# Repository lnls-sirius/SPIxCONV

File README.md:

# SPIxCONV

This project consists of an 18-bit analog input (ADC) and output (DAC) within a range of 20 V (± 10 V) and 32 digital pins that can be either as inputs or outputs. This system interfaces with pulsed power electronics hardware in order to control the output voltage for pulsed magnets as well as read and write status commands to their power supplies. An operator interface (OPI) software based on Qt was also developed for remote control.

<!--========================================-->
## Hardware
<!--========================================-->

<!--==============================-->
### Main Board
<!--==============================-->

<!--====================-->
#### Circuit
<!--====================-->

  - Board

  - CPLD

  - DAC

  - ADC

  - Digital I/O

<!--====================-->
#### PCB
<!--====================-->

<!--====================-->
#### Connectors
<!--====================-->

  - SPIxxCON

  - CPLD

  - Board Connection Link

<!--====================-->
#### Test Points
<!--====================-->

  - SPI

  - Power Voltage

  - Analog In/Out

<!--====================-->
#### BOM
<!--====================-->
Bill of materials

<!--==============================-->
### GPIO Expander Board
<!--==============================-->

<!--====================-->
#### Circuit
<!--====================-->

<!--====================-->
#### PCB
<!--====================-->

<!--====================-->
#### Connectors
<!--====================-->

  - Interface A/B

  - Interface C/D

<!--====================-->
#### Test Points
<!--====================-->

  - Power Voltage

  - Analog In/Out

<!--====================-->
#### BOM
<!--====================-->
Bill of materials

<!--====================-->
### Identification
<!--====================-->

<!--========================================-->
### Software
<!--========================================-->

The software files of this project related to the server-side (IOC) is now available at [streamdevice-ioc](https://github.com/lnls-sirius/streamdevice-ioc) GitHub's repository under the "spixconv" directory.

The software files related to the OPI (Operator Interface) is now at [pydm-opi](https://github.com/lnls-sirius/pydm-opi) GitHub's repository.

Finally, the client-side (Python code) is at this repository under the [scripts](https://github.com/lnls-sirius/SPIxCONV/tree/master/software/scripts) directory.

<!--====================-->
#### Brief Description
<!--====================-->
To remotely control the board an [EPICS](https://epics-controls.org/about-epics/) IOC with an OPI was developed.

The IOC was built using [asynDriver](https://epics.anl.gov/modules/soft/asyn/) and [StreamDevice](http://epics.web.psi.ch/software/streamdevice/) on top of it. The application is launched in a form of a Docker container. The Docker image can be found at [Docker Hub](https://hub.docker.com/repository/docker/lnlscon/streamdevice-ioc) with the tag "SPIxCONV" followed by the version (eg: SPIxCONV-v1.9.6).

To configure the parameters of the IOC a [spreadsheet](https://cnpemcamp.sharepoint.com/:x:/s/controle/EUG0_4JUaz9Au7kZNcMZwZQB1x5OJBN_1QMdbbCGJ1Driw?e=Po8LNr) is used (available for CNPEM accounts only). PV's prefix, Power Supply voltage, host IP to connect to, scan rate and other settings can be adjusted. 

<!--====================-->
#### OPI (Operator Interface)
<!--====================-->

Previously, [Control System Studio](http://controlsystemstudio.org/) was used to develop the OPI. The windows can still be found under the [CSS](https://github.com/lnls-sirius/SPIxCONV/tree/master/software/CSS) directory. Lately, we have been using [PyDM (Python Display Manager)](https://slaclab.github.io/pydm/) to develop the windows. As stated before, the files related to the PyDM OPI is located in [pydm-opi](https://github.com/lnls-sirius/pydm-opi) repository.

<!--====================-->
#### CPLD
<!--====================-->

<!--====================-->
#### Board Calibration
<!--====================-->

To achieve more confiability, a calibration is done considering the DAC adjusts and the ADC measures. The next figures show the setup for this procedure. We basically connect the DAC output to the voltmeter and to the ADC input simultaneously.

  - DAC calibration:
To calibrate the DAC we set its output to -9 V and later to +9 V and measure the real output voltage with the help of a 7 ½ digit voltmeter (here we are using the [Keysight 34420A](https://github.com/lnls-sirius/SPIxCONV/blob/master/documentation/Keysight%2034420A%20datasheet.pdf). We then use both measures to calculate the angular and linear coeffients for this curve.

  - ADC calibration:
Now that we have the DAC calibrated, we will use its output to calibrate the ADC coefficients. Again, we set the DAC output to -9 V (already considering the corrections), wait 60 s for thermal stabilization and read the voltage with the ADC. We then repeat the procedure for an adjustment of +9 V on the DAC output. Finally, these measures are used to calculate an angular and linear coefficient for the ADC.

An automated script was developed for this process. To control the voltmeter 34420A remotely we need a RS-232/USB adaptor to plug it in the USB connector of the BeagleBone Black. An important thing to note, is that the serial cable (RS-232) has an identification to show which side is the voltmeter's one and which should be connected to the adaptor.

Finally, to calibrate the board, just connect to the BeagleBone Black and run the appropriate scrips, as showed below:

```console
$ ssh root@<BBB-IP>
root@beaglebone:~# systemctl stop bbb-function
root@beaglebone:~# /root/spixconv/software/scripts/calibration.py <BOARD-ID>
    gain = 1.00014284735
    offset = -15.81235112
    gain = 1.00052568324
    offset = -66.6829873034
```

Where <BBB-IP> is the BeagleBone IP (for example "192.168.7.2") and the <BOARD-ID> is the identification of the board (for example "15").

| Board ID |   DAC gain    |  DAC offset   |   ADC gain    |   ADC offset   |    Date    |
| :------: | :-----------: | :-----------: | :-----------: | :------------: | :--------: |
|     1    | 1.00022856796 | -23.604551795 | 1.00031151483 | -25.5034979525 | 06/14/2018 |
|     2    | 1.00026576963 | -28.880179670 | 1.00047415222 | -60.2158137830 | 06/14/2018 |
|     3    | 1.00030796599 | -32.699603180 | 1.00041814300 | -47.9227113769 | 06/18/2018 |
|     4    | 1.00017479634 | -17.242341185 | 1.00026390485 | -31.6174014794 | 06/19/2018 |
|     5    | 1.00017265115 | -13.974728690 | 1.00045784906 | -39.5533800101 | 06/19/2018 |
|     6    | 1.00015184443 | -11.674423865 | 1.00060158655 | -59.1729212883 | 06/19/2018 |
|     7    | 1.00019784934 | -20.918896760 | 1.00029330340 | -24.4439584471 | 06/19/2018 |
|     8    | 1.00035674834 | -37.769448800 | 1.00029168671 | -34.0324363824 | 06/19/2018 |
|     9    | 1.00023135812 | -26.566767695 | 1.00045023944 | -44.5911926966 | 06/19/2018 |
|    10    | 1.00020592482 | -21.571632830 | 1.00044201352 | -51.3525871959 | 06/19/2018 |
|    11    | 1.00014897135 | -16.862233835 | 1.00067934214 | -81.2456900362 | 06/19/2018 |
|    12    | 1.00022598345 | -22.008100925 | 1.00057691743 | -66.0110325831 | 06/19/2018 |
|    13    | 1.00032333122 | -33.267142775 | 1.00039023957 | -45.3552208747 | 06/19/2018 |
|    14    | 1.00016016368 | -18.311884625 | 1.00048566801 | -60.5575726483 | 06/19/2018 |
|    15    | 1.00022607238 | -22.051354520 | 1.00046470661 | -58.5770907625 | 06/19/2018 |
|    16    | 1.00028974958 | -32.626203140 | 1.00073037347 | -97.7370251289 | 06/19/2018 |
|    17    | 1.00027075563 | -27.292903805 | 1.00037276504 | -34.2682222150 | 06/20/2018 |
|    18    | 1.00017256223 | -15.753368945 | 1.00046720927 | -66.4461854942 | 06/20/2018 |
|    19    | 1.00023103020 | -24.296609315 | 1.00032961706 | -28.7417520711 | 06/20/2018 |
|    20    | 1.00019010191 | -20.998850375 | 1.00012983616 | -2.10309904365 | 06/20/2018 |

<!--====================-->
#### Code
<!--====================-->
[https://lnls-sirius.github.io/SPIxCONV/](https://lnls-sirius.github.io/SPIxCONV/)

<!--========================================-->
### Known Problems
<!--========================================-->

  - Not connecting to IOC after BBB reboots:  
    Status: both nodes (IOC and BBB) show they are connected, but the IOC does not respond.
    Solution: reboot IOC.

  - Flash memory loses data:
    Status: this happened once in three years. After a power cycle, the flash suddenly lost al its data!
    Solution: record information in flash memory again.

<!--========================================-->
### FAQ
<!--========================================-->

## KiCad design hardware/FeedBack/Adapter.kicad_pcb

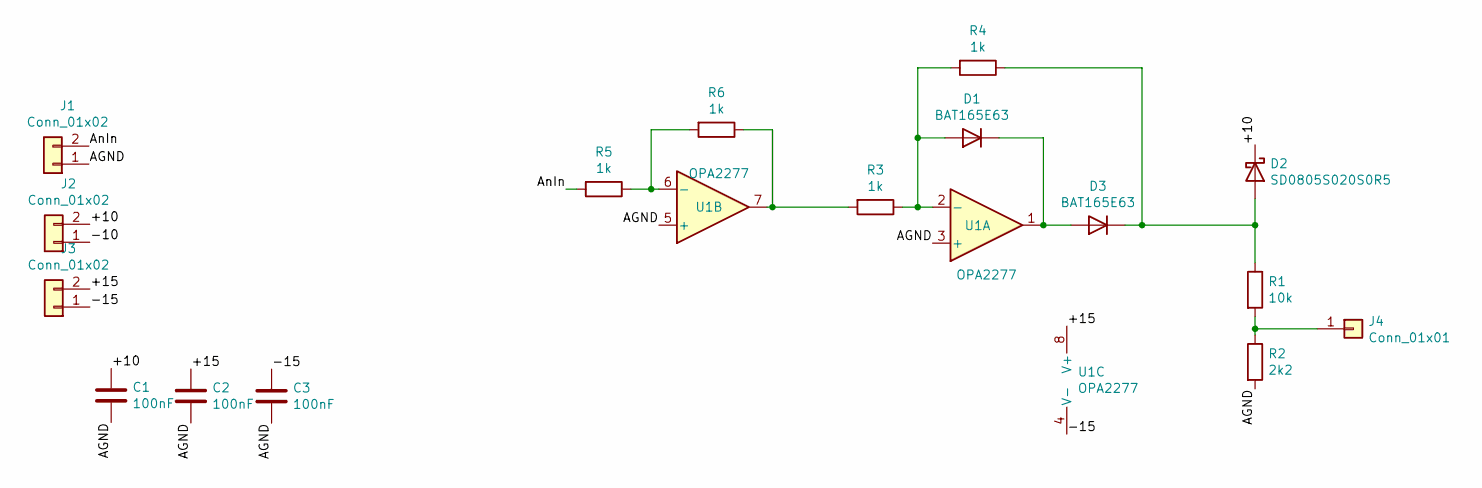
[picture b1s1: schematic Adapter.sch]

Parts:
C1, C2, C3: 100nF; C_0805_2012Metric_Pad1.18x1.45mm_HandSolder
D1, D3: BAT165E63; D_0805_2012Metric_Pad1.15x1.40mm_HandSolder
D2: SD0805S020S0R5; D_0805_2012Metric_Pad1.15x1.40mm_HandSolder
J1, J2, J3: Conn_01x02; PinSocket_1x02_P2.54mm_Vertical
J4: Conn_01x01; PinSocket_1x01_P2.54mm_Vertical
R1: 10k; R_0805_2012Metric_Pad1.20x1.40mm_HandSolder
R2: 2k2; R_0805_2012Metric_Pad1.20x1.40mm_HandSolder
R3, R4, R5, R6: 1k; R_0805_2012Metric_Pad1.20x1.40mm_HandSolder
U1: OPA2277; SOIC-8_3.9x4.9mm_P1.27mm

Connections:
/+10: C1.1, D2.1 (K), J2.2
/+15: C2.1, J3.2, U1.8 (V+)
/-10: J2.1
/-15: C3.1, J3.1, U1.4 (V-)
/AGND: C1.2, C2.2, C3.2, J1.1, R2.2, U1.3 (+), U1.5 (+)
/AnIn: J1.2, R5.2
unnamed: D1.1 (K), D3.2 (A), U1.1
unnamed: D1.2 (A), R3.1, R4.2, U1.2 (-)
unnamed: D2.2 (A), D3.1 (K), R1.1, R4.1
unnamed: J4.1, R1.2, R2.1
unnamed: R3.2, R6.1, U1.7
unnamed: R5.1, R6.2, U1.6 (-)

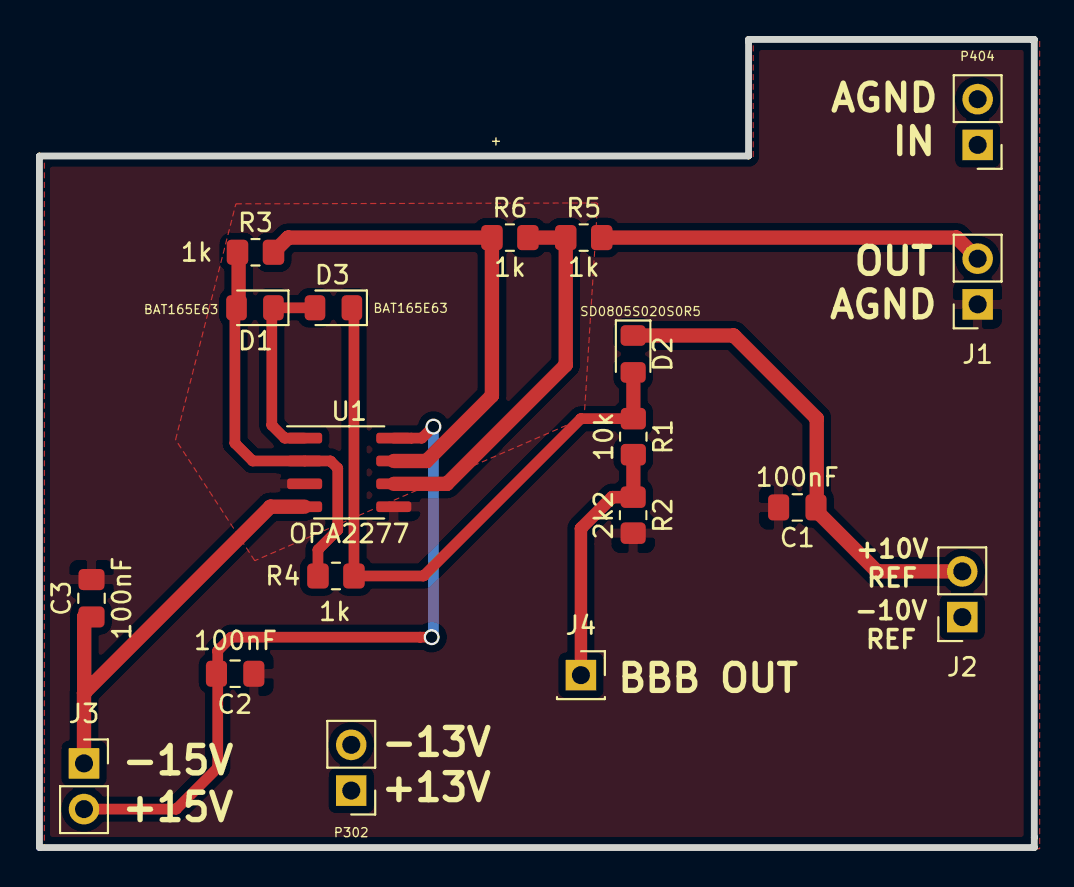
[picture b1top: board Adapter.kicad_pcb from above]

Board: 2 copper layers, 55.3 x 44.9 mm, 19 parts (0 on the bottom side), 11 nets.

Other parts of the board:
P302: CONN_01X02; Pin_Header_Straight_1x02_Pitch2.54mm
P404: Analog_in; Pin_Header_Straight_1x02_Pitch2.54mm

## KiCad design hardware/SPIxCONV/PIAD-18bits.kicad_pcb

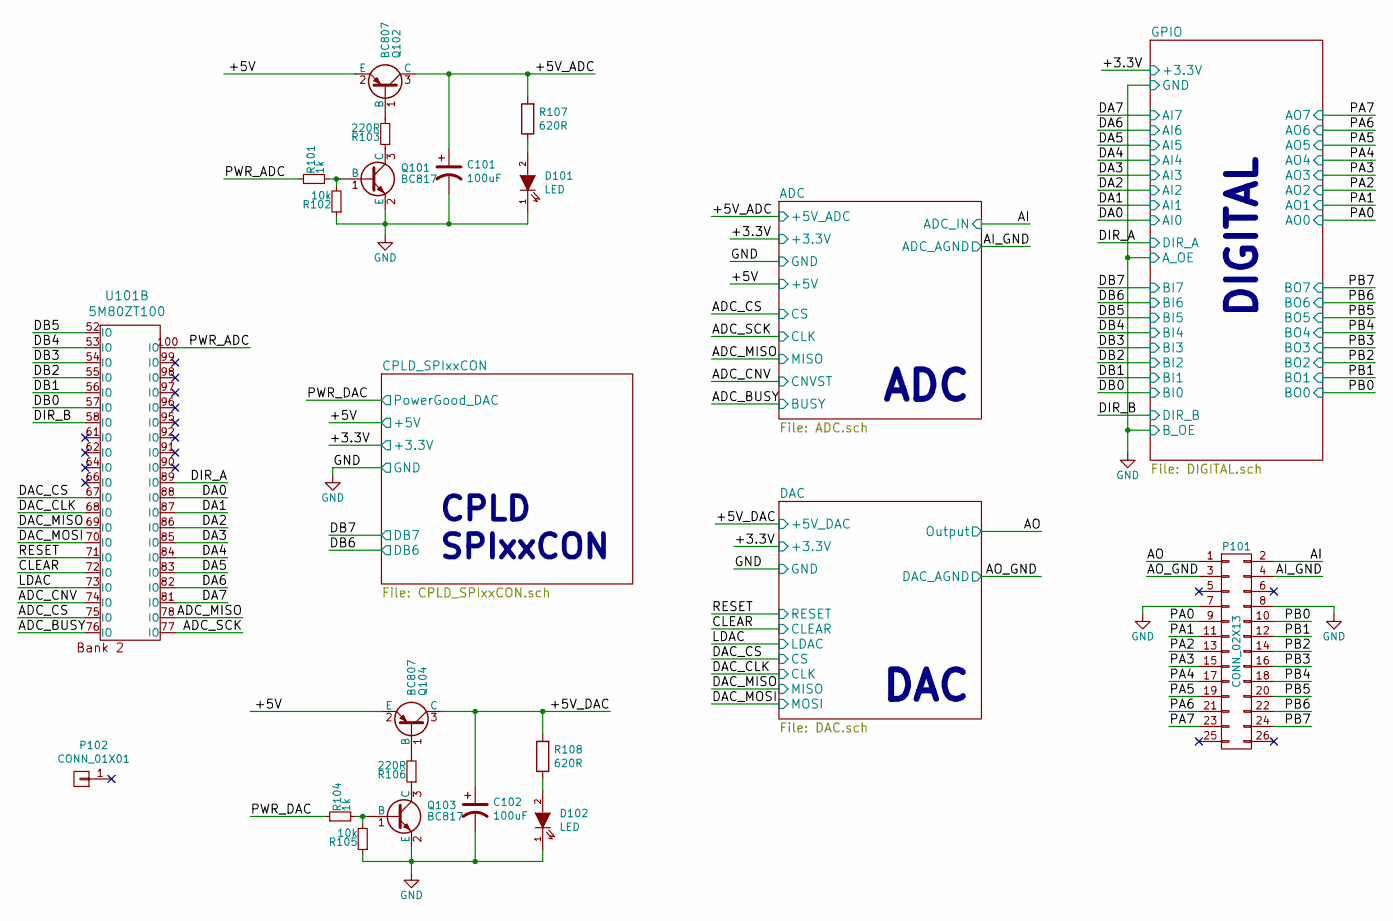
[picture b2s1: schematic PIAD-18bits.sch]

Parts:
C101, C102: 100uF; CP_Elec_6.3x5.3
D101, D102: LED; LED_0805
P101: CONN_02X13; Pin_Header_Straight_2x13_Pitch2.54mm
P102: CONN_01X01; LNLS_LOGO_Silk
Q101, Q103: BC817; SOT-23
Q102, Q104: BC807; SOT-23
R101, R104: 1k; R_0805
R102, R105: 10k; R_0805
R103, R106: 220R; R_0805
R107, R108: 620R; R_0805
U101: 5M80ZT100; TQFP-100_14x14mm_Pitch0.5mm

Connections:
+5V: Q102.2 (E), Q104.2 (E); also elsewhere on the board
/+5V_ADC: C101.1, Q102.3 (C), R107.2; also elsewhere on the board
/+5V_DAC: C102.1, Q104.3 (C), R108.2; also elsewhere on the board
/ADC_BUSY: U101.76 (IO); also elsewhere on the board
/ADC_CNV: U101.74 (IO); also elsewhere on the board
/ADC_CS: U101.75 (IO); also elsewhere on the board
/ADC_MISO: U101.78 (IO); also elsewhere on the board
/ADC_SCK: U101.77 (IO); also elsewhere on the board
/AI: P101.2; also elsewhere on the board
/AI_GND: P101.4; also elsewhere on the board
/AO: P101.1; also elsewhere on the board
/AO_GND: P101.3; also elsewhere on the board
/CLEAR: U101.72 (IO); also elsewhere on the board
/DA0: U101.88 (IO); also elsewhere on the board
/DA1: U101.87 (IO); also elsewhere on the board
/DA2: U101.86 (IO); also elsewhere on the board
/DA3: U101.85 (IO); also elsewhere on the board
/DA4: U101.84 (IO); also elsewhere on the board
/DA5: U101.83 (IO); also elsewhere on the board
/DA6: U101.82 (IO); also elsewhere on the board
/DA7: U101.81 (IO); also elsewhere on the board
/DAC_CLK: U101.68 (IO); also elsewhere on the board
/DAC_CS: U101.67 (IO); also elsewhere on the board
/DAC_MISO: U101.69 (IO); also elsewhere on the board
/DAC_MOSI: U101.70 (IO); also elsewhere on the board
/DB0: U101.57 (IO); also elsewhere on the board
/DB1: U101.56 (IO); also elsewhere on the board
/DB2: U101.55 (IO); also elsewhere on the board
/DB3: U101.54 (IO); also elsewhere on the board
/DB4: U101.53 (IO); also elsewhere on the board
/DB5: U101.52 (IO); also elsewhere on the board
/DIR_A: U101.89 (IO); also elsewhere on the board
/DIR_B: U101.58 (IO); also elsewhere on the board
/LDAC: U101.73 (IO); also elsewhere on the board
/PA0: P101.9; also elsewhere on the board
/PA1: P101.11; also elsewhere on the board
/PA2: P101.13; also elsewhere on the board
/PA3: P101.15; also elsewhere on the board
/PA4: P101.17; also elsewhere on the board
/PA5: P101.19; also elsewhere on the board
/PA6: P101.21; also elsewhere on the board
/PA7: P101.23; also elsewhere on the board
/PB0: P101.10; also elsewhere on the board
/PB1: P101.12; also elsewhere on the board
/PB2: P101.14; also elsewhere on the board
/PB3: P101.16; also elsewhere on the board
/PB4: P101.18; also elsewhere on the board
/PB5: P101.20; also elsewhere on the board
/PB6: P101.22; also elsewhere on the board
/PB7: P101.24; also elsewhere on the board
/PWR_ADC: R101.1, U101.100 (IO)
/PWR_DAC: R104.1; also elsewhere on the board
/RESET: U101.71 (IO); also elsewhere on the board
GND: C101.2, C102.2, D101.1 (K), D102.1 (K), P101.7, P101.8, Q101.2 (E), Q103.2 (E), R102.1, R105.1; also elsewhere on the board
unnamed: D101.2 (A), R107.1
unnamed: D102.2 (A), R108.1
unnamed: Q101.1 (B), R101.2, R102.2
unnamed: Q101.3 (C), R103.1
unnamed: Q102.1 (B), R103.2
unnamed: Q103.1 (B), R104.2, R105.2
unnamed: Q103.3 (C), R106.1
unnamed: Q104.1 (B), R106.2

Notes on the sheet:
DAC
ADC
DIGITAL
CPLD SPIxxCON

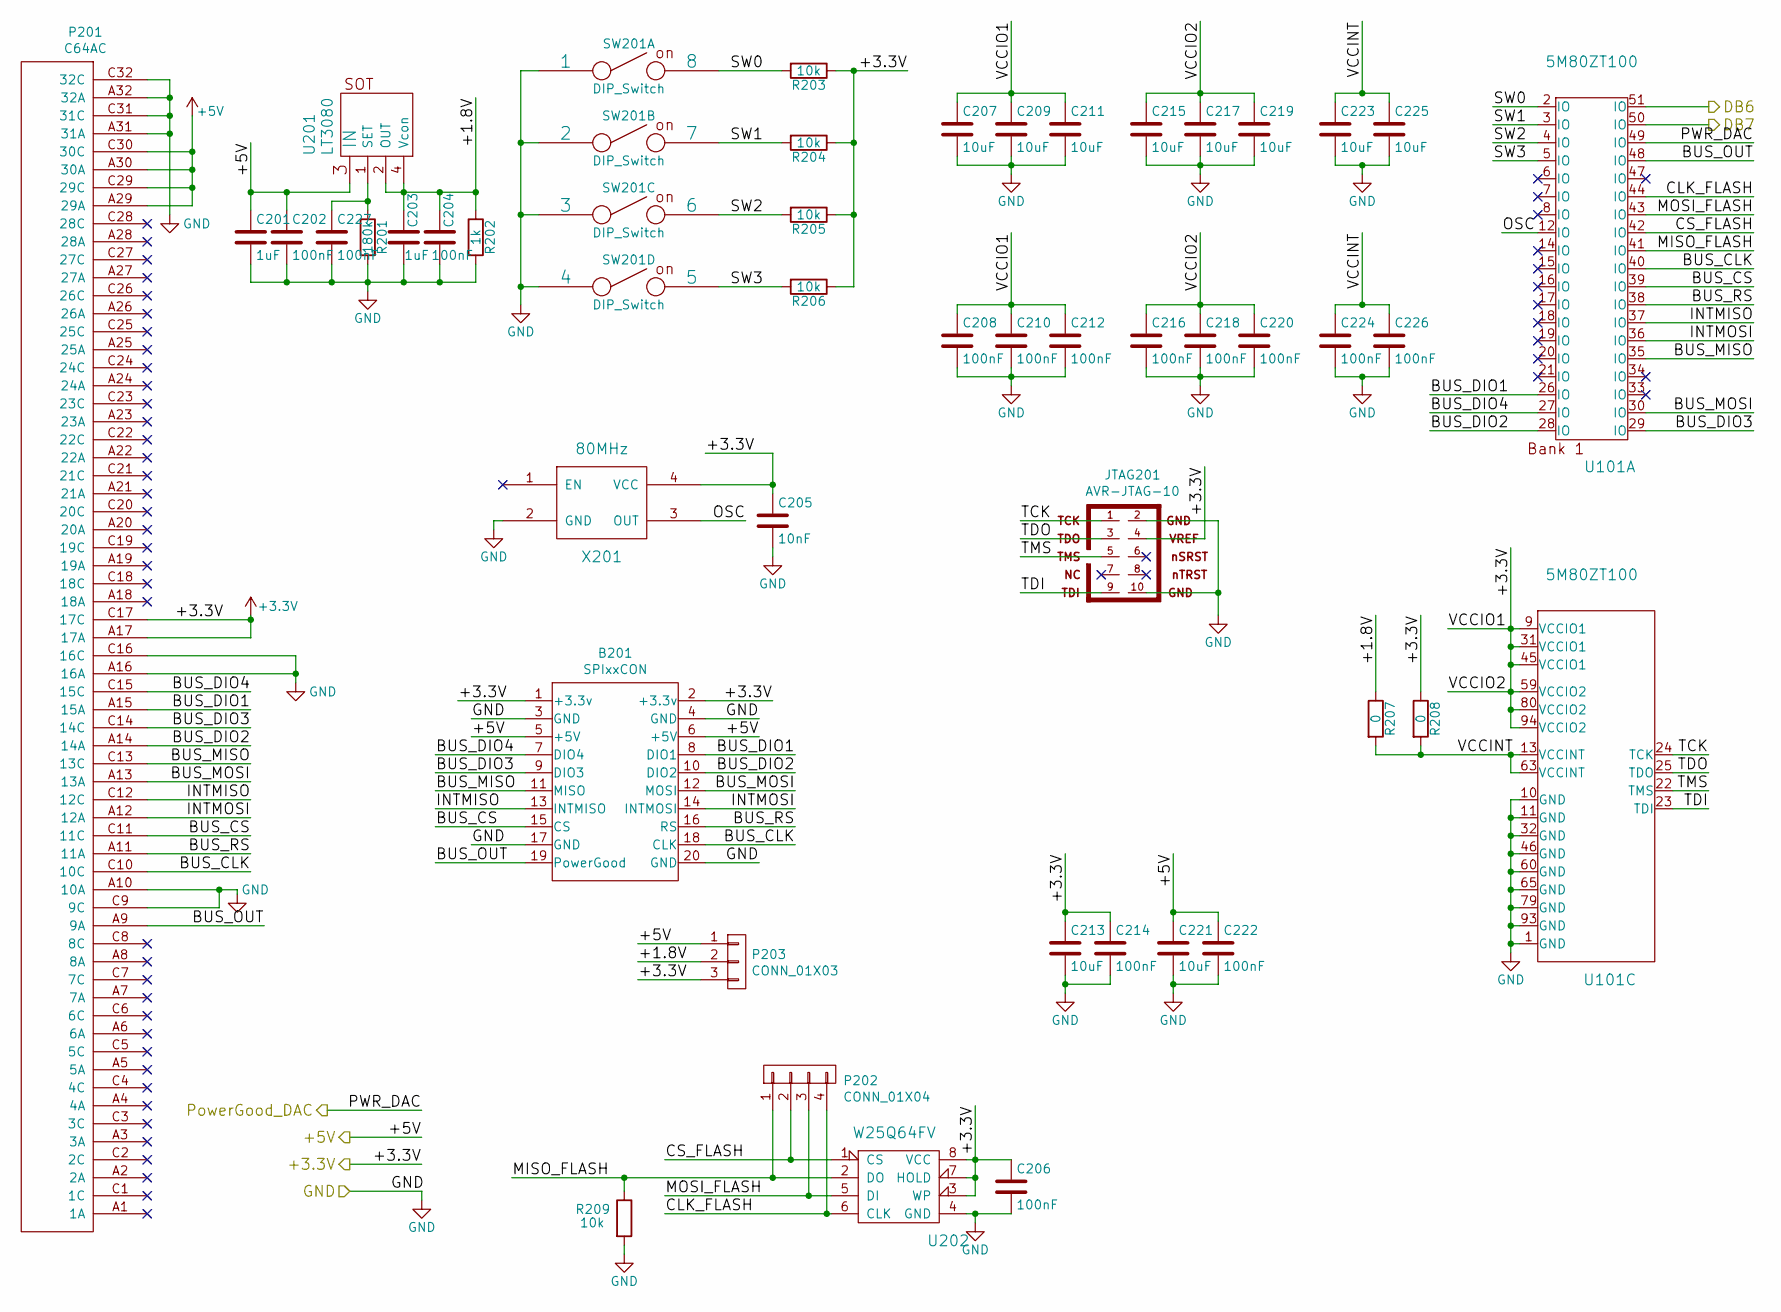
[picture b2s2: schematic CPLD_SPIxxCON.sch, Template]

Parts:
B201: SPIxxCON; SPIxxCON_(only_connector)
C201, C203: 1uF; C_0805
C202, C204, C206, C208, C210, C212, C214, C216, C218, C220, C222, C224, C226, C227: 100nF; C_0805
C205: 10nF; C_0805
C207, C209, C211, C213, C215, C217, C219, C221, C223, C225: 10uF; C_0805
JTAG201: AVR-JTAG-10; Pin_Header_Straight_2x05_Pitch2.54mm
P201: C64AC; Eurocard_template
P202: CONN_01X04; Pin_Header_Straight_1x04_Pitch2.54mm
P203: CONN_01X03; Pin_Header_Straight_1x03_Pitch2.54mm
R201: 180k; R_0805
R202: 1k; R_0805
R203, R204, R205, R206, R209: 10k; R_0805
R207, R208: 0; R_0805
SW201: DIP_Switch; DIP_switch_SPST_KAE04LGGT
U101: 5M80ZT100; TQFP-100_14x14mm_Pitch0.5mm
U201: LT3080; SOT-223
U202: W25Q64FV; SOIJ-8_5.3x5.3mm_Pitch1.27mm
X201: 80MHz; Oscilador_3.3V_HCMOS_TTL_SMD

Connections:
+3V3: B201.1 (+3.3v), B201.2 (+3.3v), C205.1, C206.1, C207.1, C208.1, C209.1, C210.1, C211.1, C212.1, C213.1, C214.1, C215.1, C216.1, C217.1, C218.1, C219.1, C220.1, JTAG201.4, P201.A17 (17A), P201.C17 (17C), P203.3, R203.1, R204.1, R205.1, R206.1, R208.1, U101.9 (VCCIO1), U101.31 (VCCIO1), U101.45 (VCCIO1), U101.59 (VCCIO2), U101.80 (VCCIO2), U101.94 (VCCIO2), U202.3 (WP), U202.7 (HOLD), U202.8 (VCC), X201.4 (VCC); also elsewhere on the board
+5V: B201.5 (+5V), B201.6 (+5V), C201.1, C202.1, C221.1, C222.1, P201.A29 (29A), P201.A30 (30A), P201.C29 (29C), P201.C30 (30C), P203.1, U201.3 (IN); also elsewhere on the board
/CPLD_SPIxxCON/+1.8V: C203.1, C204.1, P203.2, R202.1, R207.1, U201.2 (OUT), U201.4 (Vcon)
/CPLD_SPIxxCON/BUS_CLK: B201.18 (CLK), P201.C10 (10C), U101.40 (IO)
/CPLD_SPIxxCON/BUS_CS: B201.15 (CS), P201.C11 (11C), U101.39 (IO)
/CPLD_SPIxxCON/BUS_DIO1: B201.8 (DIO1), P201.A15 (15A), U101.26 (IO)
/CPLD_SPIxxCON/BUS_DIO2: B201.10 (DIO2), P201.A14 (14A), U101.28 (IO)
/CPLD_SPIxxCON/BUS_DIO3: B201.9 (DIO3), P201.C14 (14C), U101.29 (IO)
/CPLD_SPIxxCON/BUS_DIO4: B201.7 (DIO4), P201.C15 (15C), U101.27 (IO)
/CPLD_SPIxxCON/BUS_MISO: B201.11 (MISO), P201.C13 (13C), U101.35 (IO)
/CPLD_SPIxxCON/BUS_MOSI: B201.12 (MOSI), P201.A13 (13A), U101.30 (IO)
/CPLD_SPIxxCON/BUS_OUT: B201.19 (PowerGood), P201.A9 (9A), U101.48 (IO)
/CPLD_SPIxxCON/BUS_RS: B201.16 (RS), P201.A11 (11A), U101.38 (IO)
/CPLD_SPIxxCON/CLK_FLASH: P202.4, U101.44 (IO), U202.6 (CLK)
/CPLD_SPIxxCON/CS_FLASH: P202.2, U101.42 (IO), U202.1 (CS)
/CPLD_SPIxxCON/INTMISO: B201.13 (INTMISO), P201.C12 (12C), U101.37 (IO)
/CPLD_SPIxxCON/INTMOSI: B201.14 (INTMOSI), P201.A12 (12A), U101.36 (IO)
/CPLD_SPIxxCON/MISO_FLASH: P202.1, R209.1, U101.41 (IO), U202.2 (DO)
/CPLD_SPIxxCON/MOSI_FLASH: P202.3, U101.43 (IO), U202.5 (DI)
/CPLD_SPIxxCON/OSC: U101.12 (IO), X201.3 (OUT)
/CPLD_SPIxxCON/SW0: R203.2, SW201.8, U101.2 (IO)
/CPLD_SPIxxCON/SW1: R204.2, SW201.7, U101.3 (IO)
/CPLD_SPIxxCON/SW2: R205.2, SW201.6, U101.4 (IO)
/CPLD_SPIxxCON/SW3: R206.2, SW201.5, U101.5 (IO)
/CPLD_SPIxxCON/TCK: JTAG201.1, U101.24 (TCK)
/CPLD_SPIxxCON/TDI: JTAG201.9, U101.23 (TDI)
/CPLD_SPIxxCON/TDO: JTAG201.3, U101.25 (TDO)
/CPLD_SPIxxCON/TMS: JTAG201.5, U101.22 (TMS)
/CPLD_SPIxxCON/VCCINT: C223.1, C224.1, C225.1, C226.1, R207.2, R208.2, U101.13 (VCCINT), U101.63 (VCCINT)
/DB6: U101.51 (IO); also elsewhere on the board
/DB7: U101.50 (IO); also elsewhere on the board
/PWR_DAC: U101.49 (IO); also elsewhere on the board
GND: B201.3 (GND), B201.4 (GND), B201.17 (GND), B201.20 (GND), C201.2, C202.2, C203.2, C204.2, C205.2, C206.2, C207.2, C208.2, C209.2, C210.2, C211.2, C212.2, C213.2, C214.2, C215.2, C216.2, C217.2, C218.2, C219.2, C220.2, C221.2, C222.2, C223.2, C224.2, C225.2, C226.2, C227.2, JTAG201.2, JTAG201.10, P201.A10 (10A), P201.A16 (16A), P201.A31 (31A), P201.A32 (32A), P201.C9 (9C), P201.C16 (16C), P201.C31 (31C), P201.C32 (32C), R201.2, R202.2, R209.2, SW201.1, SW201.2, SW201.3, SW201.4, U101.1 (GND), U101.10 (GND), U101.11 (GND), U101.32 (GND), U101.46 (GND), U101.60 (GND), U101.65 (GND), U101.79 (GND), U101.93 (GND), U202.4 (GND), X201.2 (GND); also elsewhere on the board
unnamed: C227.1, R201.1, U201.1 (SET)

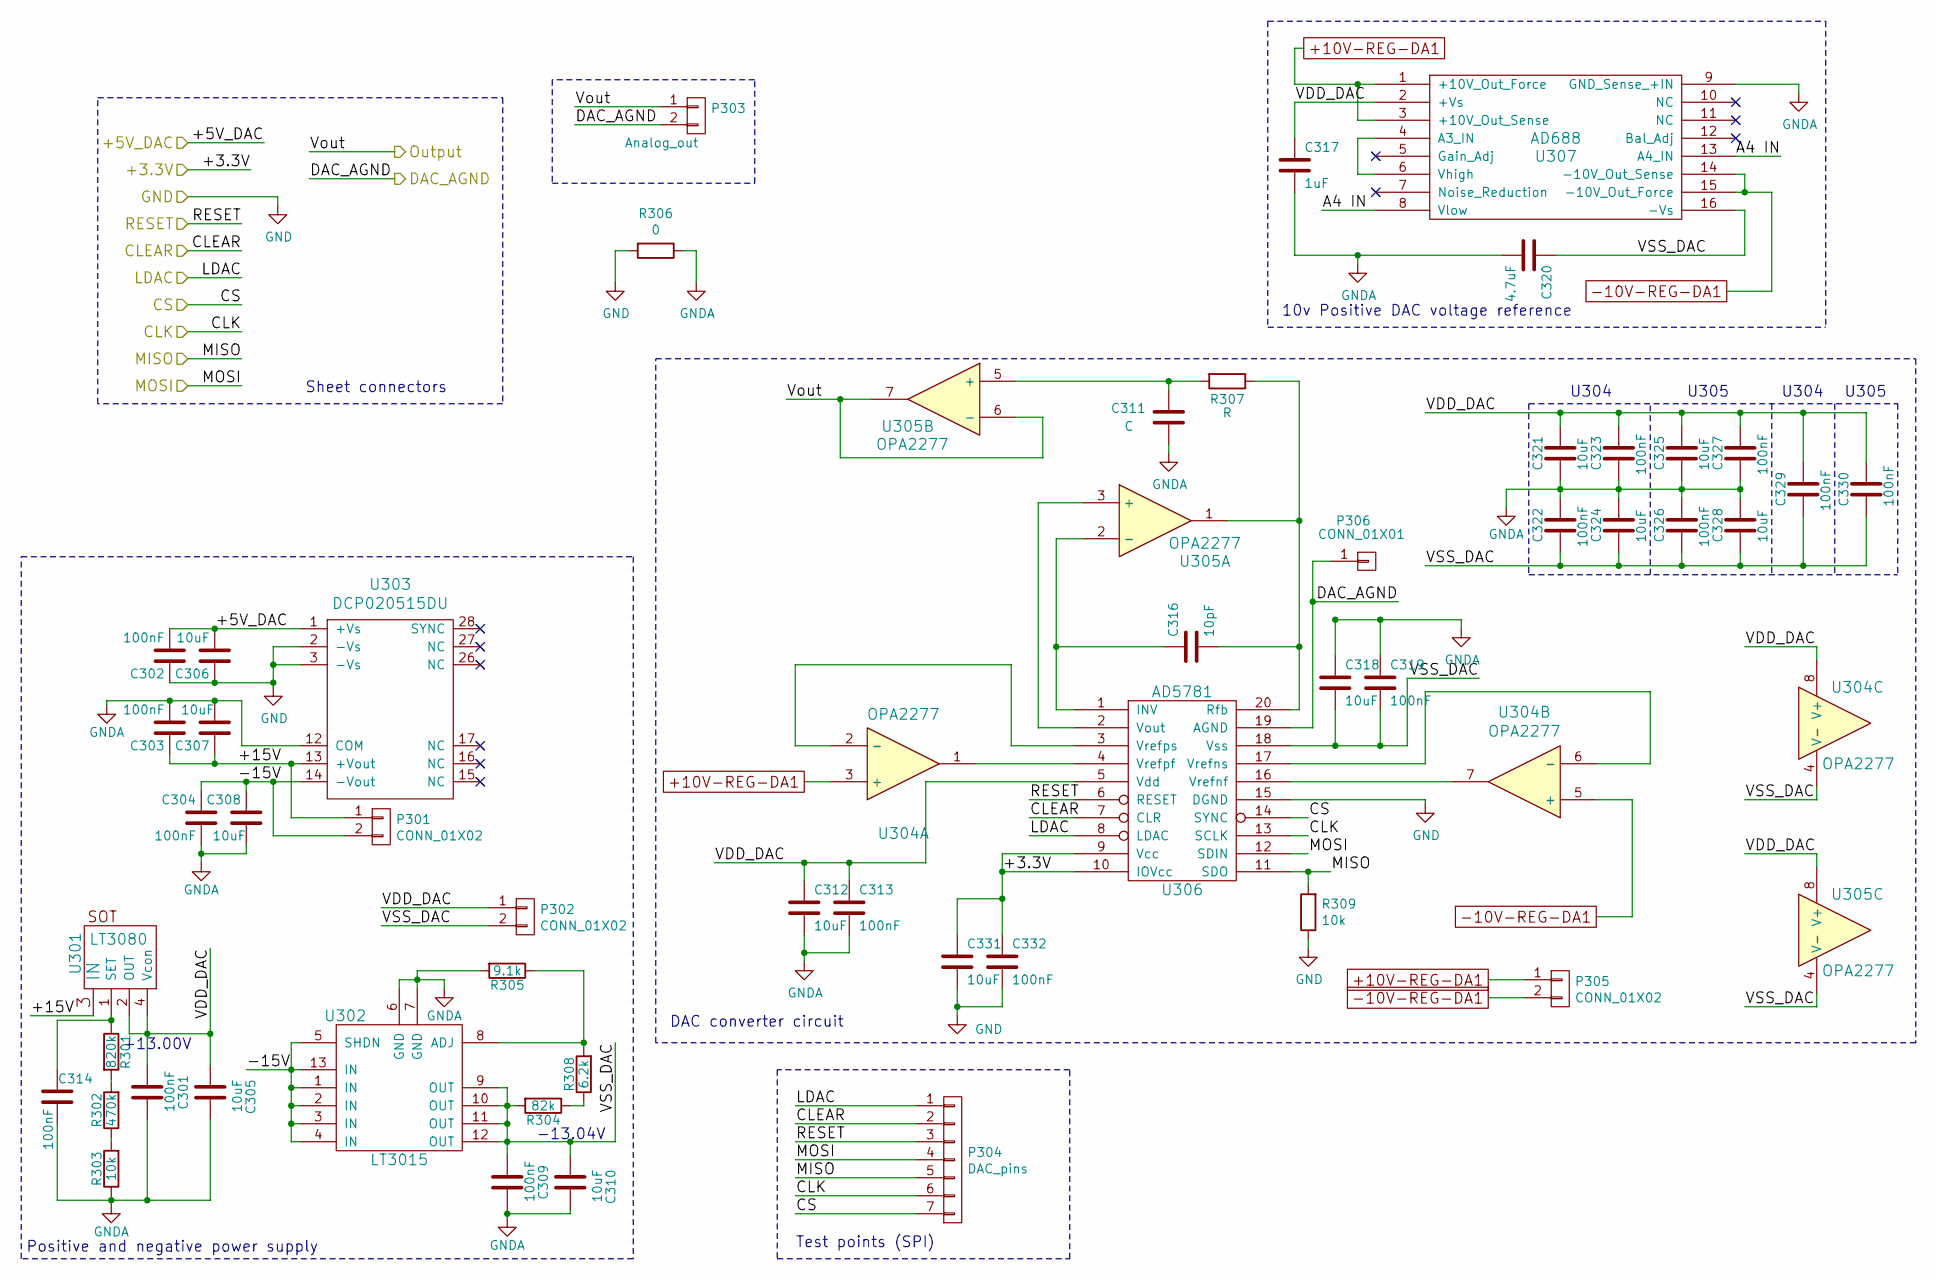
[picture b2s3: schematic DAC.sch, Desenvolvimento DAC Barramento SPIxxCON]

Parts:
C301, C302, C309, C313, C314, C319, C322, C323, C326, C327, C329, C330, C332: 100nF; C_0805
C303, C304: 100nF; C_0603
C305, C306, C310, C312, C318, C321, C324, C325, C328, C331: 10uF; C_0805
C307, C308: 10uF; CP_Elec_6.3x5.3
C311: C; C_0805
C316: 10pF; C_0805
C317: 1uF; C_0805
C320: 4.7uF; C_1210
P301, P302, P305: CONN_01X02; Pin_Header_Straight_1x02_Pitch2.54mm
P303: Analog_out; Pin_Header_Straight_1x02_Pitch2.54mm
P304: DAC_pins; Pin_Header_Straight_1x07_Pitch2.54mm
P306: CONN_01X01; ground_plane_via
R301: 820k; R_0805
R302: 470k; R_0805
R303, R309: 10k; R_0805
R304: 82k; R_0805
R305: 9.1k; R_0805
R306: 0; R_0805
R307: R; R_0805
R308: 6.2k; R_0805
U301: LT3080; SOT-223
U302: LT3015; MSOP-12-1EP_3x4mm_Pitch0.65mm
U303: DCP020515DU; DCR01XXXXU
U304, U305: OPA2277; SOIC-8_3.9x4.9mm_Pitch1.27mm
U306: AD5781; TSSOP-20_4.4x6.5mm_Pitch0.65mm
U307: AD688; AD688_(SO16W)

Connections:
+3V3: C331.1, C332.1, U306.9 (Vcc), U306.10 (IOVcc); also elsewhere on the board
+10V-REG-DA1: P305.1, U304.3 (+), U307.1 (+10V_Out_Force), U307.3 (+10V_Out_Sense)
-10V-REG-DA1: P305.2, U304.5 (+), U307.14 (-10V_Out_Sense), U307.15 (-10V_Out_Force)
/+5V_DAC: C302.2, C306.2, U303.1 (+Vs); also elsewhere on the board
/AO: P303.1, U305.6 (-), U305.7; also elsewhere on the board
/AO_GND: P303.2, P306.1, P306.2, U306.19 (AGND); also elsewhere on the board
/CLEAR: P304.2, U306.7 (CLR); also elsewhere on the board
/DAC/+15V: C303.1, C307.1, P301.1, U301.3 (IN), U303.13 (+Vout)
/DAC/-15V: C304.1, C308.1, P301.2, U302.1 (IN), U302.2 (IN), U302.3 (IN), U302.4 (IN), U302.5 (SHDN), U302.13 (IN), U303.14 (-Vout)
/DAC/A4 IN: U307.8 (Vlow), U307.13 (A4_IN)
/DAC/VDD_DAC: C301.2, C305.2, C312.1, C313.1, C317.1, C321.1, C323.1, C325.1, C327.1, C329.1, C330.1, P302.1, U301.2 (OUT), U301.4 (Vcon), U304.8 (V+), U305.8 (V+), U306.5 (Vdd), U307.2 (+Vs)
/DAC/VSS_DAC: C309.2, C310.2, C318.2, C319.2, C320.1, C322.2, C324.2, C326.2, C328.2, C329.2, C330.2, P302.2, R304.2, U302.9 (OUT), U302.10 (OUT), U302.11 (OUT), U302.12 (OUT), U304.4 (V-), U305.4 (V-), U306.18 (Vss), U307.16 (-Vs)
/DAC_CLK: P304.6, U306.13 (SCLK); also elsewhere on the board
/DAC_CS: P304.7, U306.14 (SYNC); also elsewhere on the board
/DAC_MISO: P304.5, R309.2, U306.11 (SDO); also elsewhere on the board
/DAC_MOSI: P304.4, U306.12 (SDIN); also elsewhere on the board
/LDAC: P304.1, U306.8 (LDAC); also elsewhere on the board
/RESET: P304.3, U306.6 (RESET); also elsewhere on the board
GND: C302.1, C306.1, C331.2, C332.2, R306.2, R309.1, U303.2 (-Vs), U303.3 (-Vs), U306.15 (DGND); also elsewhere on the board
GNDA: C301.1, C303.2, C304.2, C305.1, C307.2, C308.2, C309.1, C310.1, C311.2, C312.2, C313.2, C314.2, C317.2, C318.1, C319.1, C320.2, C321.2, C322.1, C323.2, C324.1, C325.2, C326.1, C327.2, C328.1, R303.1, R305.2, R306.1, U302.6 (GND), U302.7 (GND), U303.12 (COM), U307.9 (GND_Sense_+IN); also elsewhere on the board
unnamed: C311.1, R307.2, U305.5 (+)
unnamed: C314.1, R301.1, U301.1 (SET)
unnamed: C316.1, U305.2 (-), U306.1 (INV)
unnamed: C316.2, R307.1, U305.1, U306.20 (Rfb)
unnamed: R301.2, R302.2
unnamed: R302.1, R303.2
unnamed: R304.1, R308.1
unnamed: R305.1, R308.2, U302.8 (ADJ)
unnamed: U304.1, U306.4 (Vrefpf)
unnamed: U304.2 (-), U306.3 (Vrefps)
unnamed: U304.6 (-), U306.17 (Vrefns)
unnamed: U304.7, U306.16 (Vrefnf)
unnamed: U305.3 (+), U306.2 (Vout)
unnamed: U307.4 (A3_IN), U307.6 (Vhigh)

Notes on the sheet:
DAC converter circuit
10v Positive DAC voltage reference
Positive and negative power supply
+13.00V
-13.04V
Sheet connectors
Test points (SPI)
U304
U305

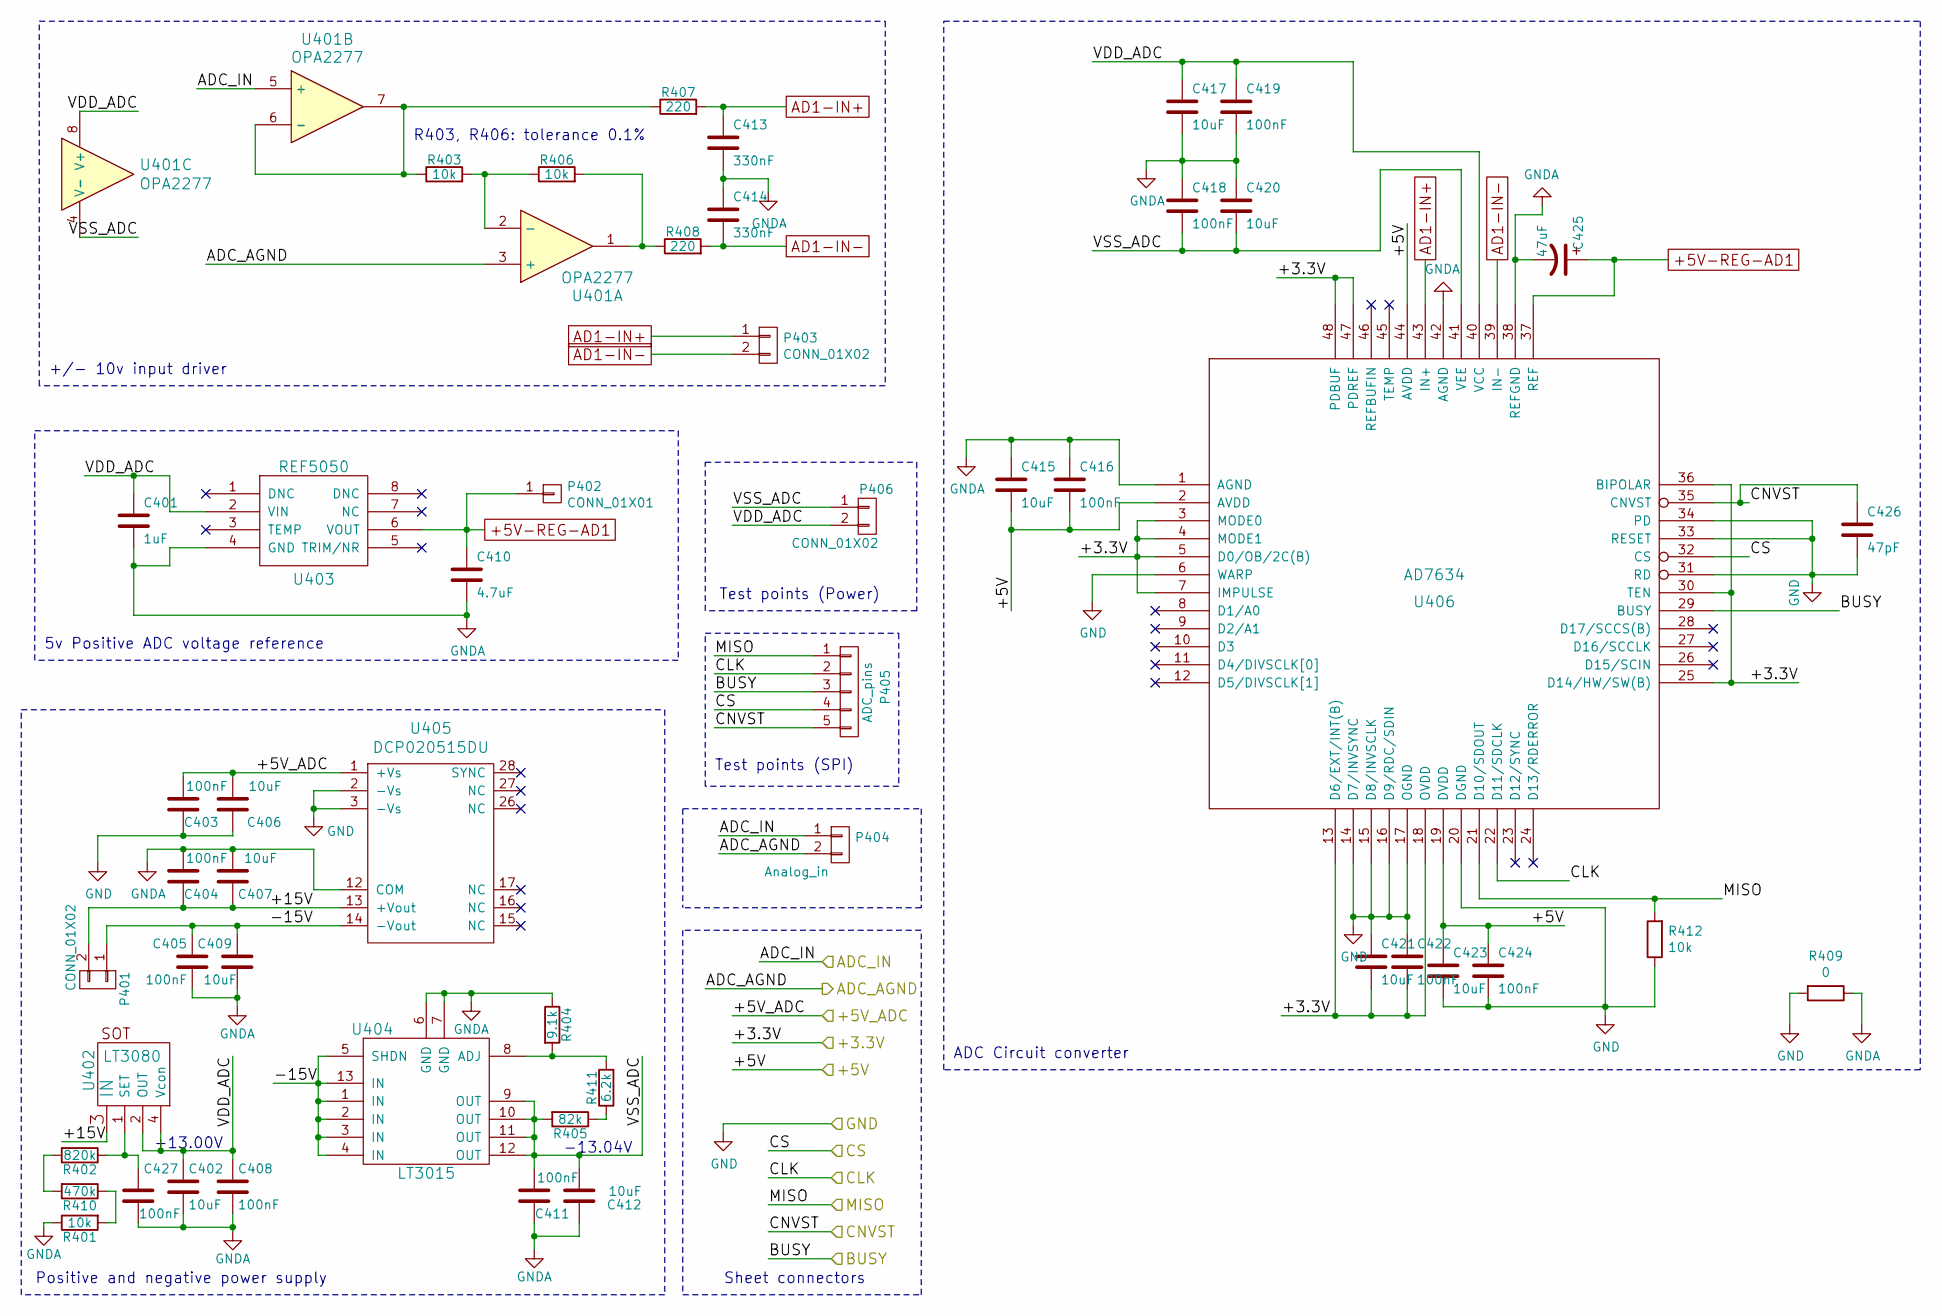
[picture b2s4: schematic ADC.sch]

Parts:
C401: 1uF; C_0805
C402, C406, C412, C415, C417, C420, C421, C423: 10uF; C_0805
C403, C408, C411, C416, C418, C419, C422, C424, C427: 100nF; C_0805
C404, C405: 100nF; C_0603
C407, C409: 10uF; CP_Elec_6.3x5.3
C410: 4.7uF; C_1210
C413, C414: 330nF; C_0805
C425: 47uF; CP_Elec_6.3x5.3
C426: 47pF; C_0805
P401, P403, P406: CONN_01X02; Pin_Header_Straight_1x02_Pitch2.54mm
P402: CONN_01X01; Pin_Header_Straight_1x01_Pitch2.54mm
P404: Analog_in; Pin_Header_Straight_1x02_Pitch2.54mm
P405: ADC_pins; Pin_Header_Straight_1x05_Pitch2.54mm
R401, R403, R406, R412: 10k; R_0805
R402: 820k; R_0805
R404: 9.1k; R_0805
R405: 82k; R_0805
R407, R408: 220; R_0805
R409: 0; R_0805
R410: 470k; R_0805
R411: 6.2k; R_0805
U401: OPA2277; SOIC-8_3.9x4.9mm_Pitch1.27mm
U402: LT3080; SOT-223
U403: REF5050; SOIC-8_3.9x4.9mm_Pitch1.27mm
U404: LT3015; MSOP-12-1EP_3x4mm_Pitch0.65mm
U405: DCP020515DU; DCR01XXXXU
U406: AD7634; LQFP-48_7x7mm_Pitch0.5mm

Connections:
+3V3: C421.2, C422.2, U406.3 (MODE0), U406.4 (MODE1), U406.5 (D0/OB/2C(B)), U406.7 (IMPULSE), U406.13 (D6/EXT/INT(B)), U406.18 (OVDD), U406.25 (D14/HW/SW(B)), U406.30 (TEN), U406.36 (BIPOLAR), U406.47 (PDREF), U406.48 (PDBUF); also elsewhere on the board
+5V: C415.2, C416.2, C423.1, C424.1, U406.2 (AVDD), U406.19 (DVDD), U406.44 (AVDD); also elsewhere on the board
+5V-REG-AD1: C410.1, C425.1, P402.1, U403.6 (VOUT), U406.37 (REF)
/+5V_ADC: C403.2, C406.2, U405.1 (+Vs); also elsewhere on the board
/ADC/+15V: C404.1, C407.1, P401.2, U402.3 (IN), U405.13 (+Vout)
/ADC/-15V: C405.1, C409.1, P401.1, U404.1 (IN), U404.2 (IN), U404.3 (IN), U404.4 (IN), U404.5 (SHDN), U404.13 (IN), U405.14 (-Vout)
/ADC/VDD_ADC: C401.1, C402.1, C408.1, C417.1, C419.1, P406.2, U401.8 (V+), U402.2 (OUT), U402.4 (Vcon), U403.2 (VIN), U406.40 (VCC)
/ADC/VSS_ADC: C411.2, C412.2, C418.2, C420.2, P406.1, R405.2, U401.4 (V-), U404.9 (OUT), U404.10 (OUT), U404.11 (OUT), U404.12 (OUT), U406.41 (VEE)
/ADC_BUSY: P405.3, U406.29 (BUSY); also elsewhere on the board
/ADC_CNV: C426.1, P405.5, U406.35 (CNVST); also elsewhere on the board
/ADC_CS: P405.4, U406.32 (CS); also elsewhere on the board
/ADC_MISO: P405.1, R412.2, U406.21 (D10/SDOUT); also elsewhere on the board
/ADC_SCK: P405.2, U406.22 (D11/SDCLK); also elsewhere on the board
/AI: P404.1, U401.5 (+); also elsewhere on the board
/AI_GND: P404.2, U401.3 (+); also elsewhere on the board
AD1-IN+: C413.1, P403.1, R407.2, U406.43 (IN+)
AD1-IN-: C414.2, P403.2, R408.2, U406.39 (IN-)
GND: C403.1, C406.1, C421.1, C422.1, C423.2, C424.2, C426.2, R409.2, R412.1, U405.2 (-Vs), U405.3 (-Vs), U406.6 (WARP), U406.14 (D7/INVSYNC), U406.15 (D8/INVSCLK), U406.16 (D9/RDC/SDIN), U406.17 (OGND), U406.20 (DGND), U406.31 (RD), U406.33 (RESET), U406.34 (PD); also elsewhere on the board
GNDA: C401.2, C402.2, C404.2, C405.2, C407.2, C408.2, C409.2, C410.2, C411.1, C412.1, C413.2, C414.1, C415.1, C416.1, C417.2, C418.1, C419.2, C420.1, C425.2, C427.2, R401.1, R404.1, R409.1, U403.4 (GND), U404.6 (GND), U404.7 (GND), U405.12 (COM), U406.1 (AGND), U406.38 (REFGND), U406.42 (AGND); also elsewhere on the board
unnamed: C427.1, R402.1, U402.1 (SET)
unnamed: R401.2, R410.1
unnamed: R402.2, R410.2
unnamed: R403.1, R407.1, U401.6 (-), U401.7
unnamed: R403.2, R406.1, U401.2 (-)
unnamed: R404.2, R411.2, U404.8 (ADJ)
unnamed: R405.1, R411.1
unnamed: R406.2, R408.1, U401.1

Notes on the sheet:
5v Positive ADC voltage reference
Positive and negative power supply
-13.04V
+/- 10v input driver
ADC Circuit converter
Sheet connectors
Test points (SPI)
Test points (Power)
R403, R406: tolerance 0.1%
+13.00V
